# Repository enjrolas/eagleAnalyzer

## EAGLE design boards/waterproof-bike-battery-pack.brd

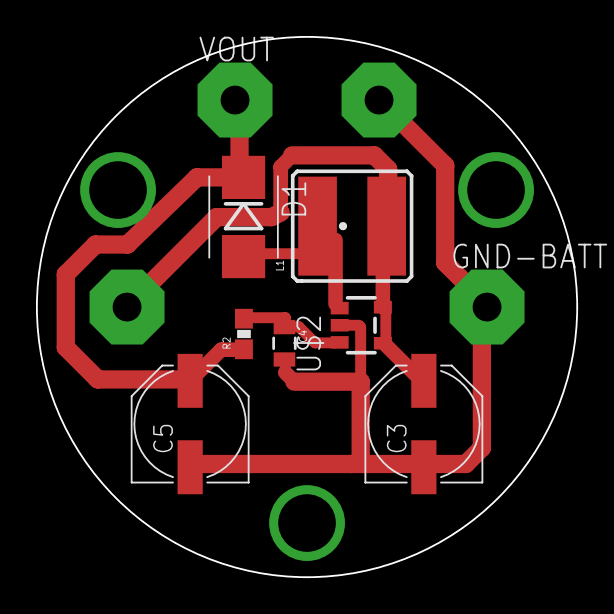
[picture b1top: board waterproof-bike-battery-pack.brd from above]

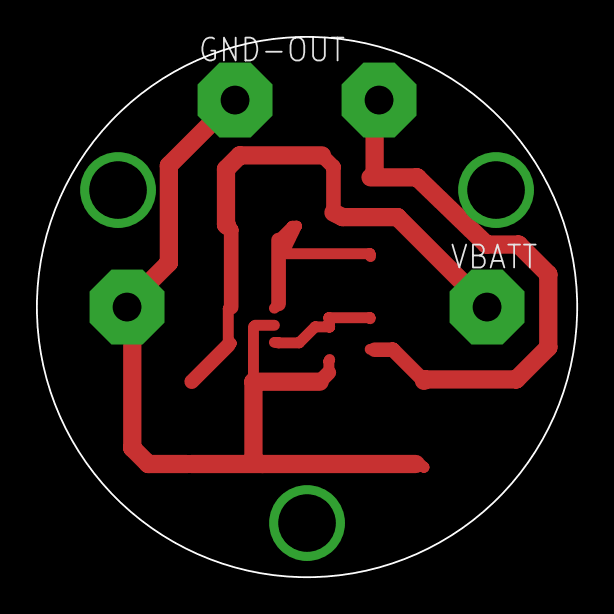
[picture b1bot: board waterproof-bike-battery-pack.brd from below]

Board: 2 copper layers, 30.0 x 30.0 mm, 11 parts (2 on the bottom side), 5 nets.

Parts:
C3, C5: 100uF; PANASONIC_D
C4: 1uF; 0805
D1: ZHCS2000; SMB-DIODE
GND-BATT: 4,16O1,6
GND-OUT: 4,16O1,6
L1: 10uH; CR54
R2: 10; 0603-RES
U$2: SP6641B-L-5-0; SOT23-5
VBATT: 4,16O1,6
VOUT: 4,16O1,6

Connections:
GND: C3.-, C4.2, C5.-, GND-BATT.1, GND-OUT.1, U$2.2
LX: D1.A, L1.P$1, U$2.1
VBATT: C3.+, L1.P$2, U$2.4, U$2.5, VBATT.1
VBOOST: C5.+, D1.C, R2.1, VOUT.1
VOUT: C4.1, R2.2, U$2.3

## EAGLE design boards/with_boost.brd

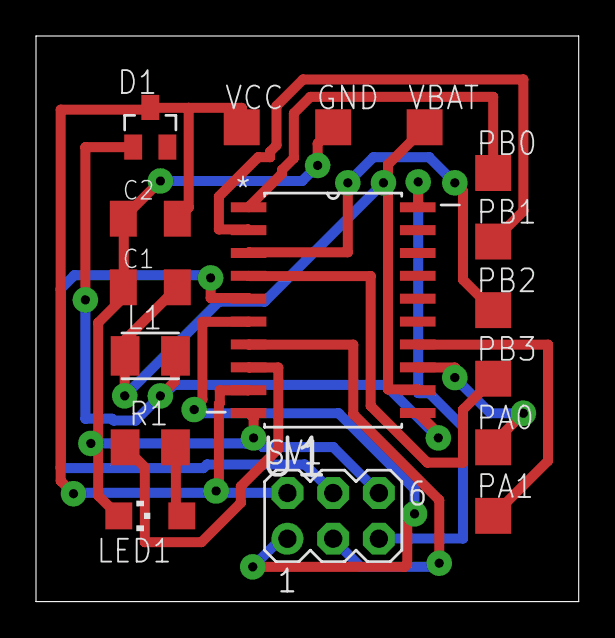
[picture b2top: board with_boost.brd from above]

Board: 2 copper layers, 30.1 x 31.4 mm, 17 parts (0 on the bottom side), 16 nets.

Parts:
C1: 4.7uf; C1206K
C2: 10uf ceramic; C1206K
D1: BAS40; SOT23
GND: TPSQTP20SQ; TP20SQ
L1: 10uh; L3225M
LED1: CHIPLED_1206
PA0, PA1: TPSQTP20SQ; TP20SQ
PB0, PB1, PB2, PB3: TPSQTP20SQ; TP20SQ
R1: 330; M1206
SV1: MA03-2
U1: ATTINY43U; SOIC127P1032X265-20N
VBAT: TPSQTP20SQ; TP20SQ
VCC: TPSQTP20SQ; TP20SQ

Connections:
GND: C1.1, C2.1, GND.TP, LED1.C, SV1.6, U1.10
unnamed: LED1.A, R1.2
unnamed: D1.1, L1.2, U1.11
unnamed: R1.1, U1.8
PA0: PA0.TP, U1.13
PA1: PA1.TP, U1.14
PA7: SV1.5, U1.20
PB0: PB0.TP, U1.1
PB1: PB1.TP, U1.2
PB2: PB2.TP, U1.3
PB3: PB3.TP, U1.4
PB4: SV1.4, U1.5
PB5: SV1.1, U1.6
PB6: SV1.3, U1.7
VBAT: C1.2, L1.1, U1.12, VBAT.TP
VCC: C2.2, D1.3, SV1.2, U1.9, VCC.TP

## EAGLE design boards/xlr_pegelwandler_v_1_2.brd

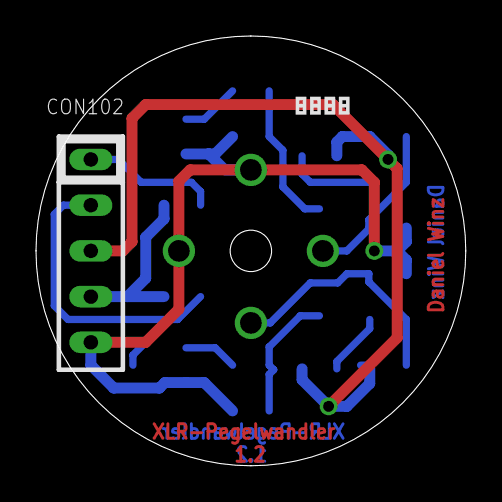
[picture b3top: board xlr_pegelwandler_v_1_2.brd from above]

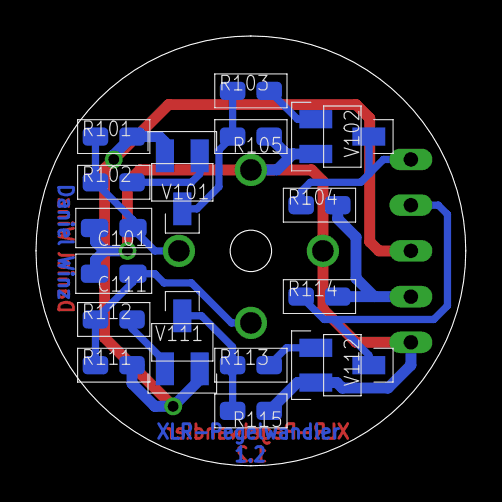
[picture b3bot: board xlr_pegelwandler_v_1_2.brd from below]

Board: 2 copper layers, 23.9 x 23.9 mm, 19 parts (16 on the bottom side), 13 nets.

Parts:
C101, C111: 100n; C_0805
CON101: XLR_NC3MD-V_NEUTRIK
CON102: CON_5X1_100MIL
R101, R111: 330; R_0805
R102, R112: 820k; R_0805
R103, R113: 330k; R_0805
R104, R114: 10k; R_0805
R105, R115: 24k; R_0805
U$1: LP_NUMBER08_SILK_TOP; LP_NUMBER_SILK_TOP
V101, V111: BC857A; SOT23
V102, V112: BC847A; SOT23

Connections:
CON101: C101.P$1, CON101.2, R101.P$1, R102.P$1
unnamed: R103.P$2, V102.1
unnamed: R113.P$2, V112.1
unnamed: CON102.P$2, R114.P$1, V112.3
unnamed: CON102.P$1, R104.P$1, V102.3
unnamed: R102.P$2, V101.1
unnamed: R103.P$1, R105.P$2, V101.3
unnamed: R113.P$1, R115.P$2, V111.3
unnamed: CON102.P$3, R101.P$2, R111.P$2, V101.2, V111.2
unnamed: R112.P$2, V111.1
unnamed: C111.P$1, CON101.3, R111.P$1, R112.P$1
unnamed: CON102.P$4, R104.P$2, R114.P$2
V102: C101.P$2, C111.P$2, CON101.1, CON101.G, CON102.P$5, R105.P$1, R115.P$1, V102.2, V112.2

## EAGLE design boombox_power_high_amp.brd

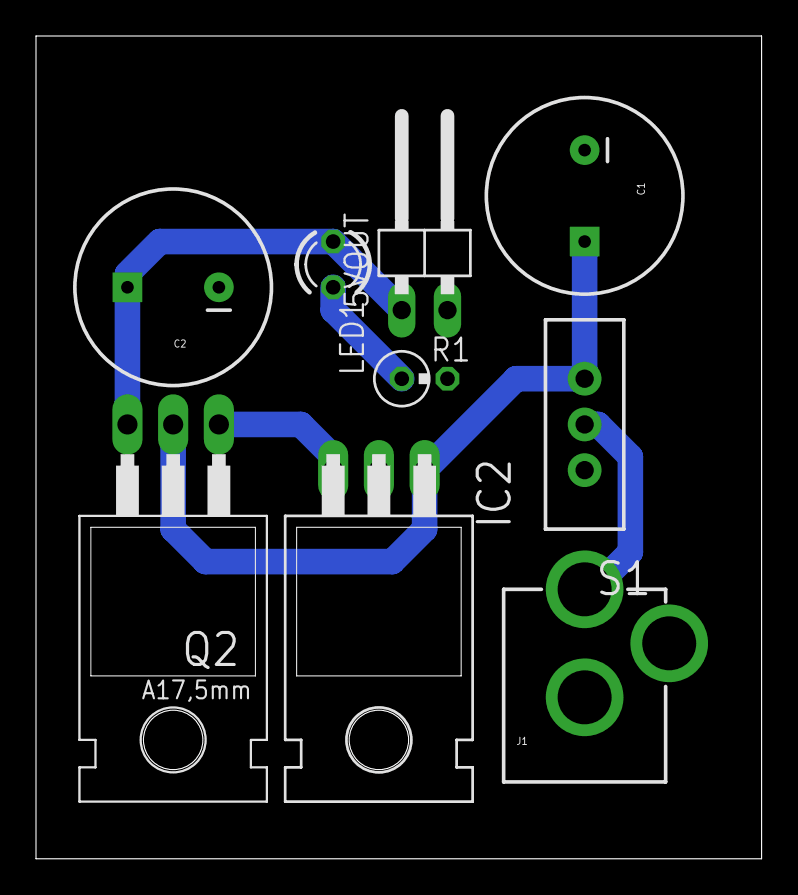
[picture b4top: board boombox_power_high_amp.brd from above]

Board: 2 copper layers, 40.3 x 45.7 mm, 9 parts (0 on the bottom side), 6 nets.

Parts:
5VOUT: 1X02/90
C1, C2: 2200uF; CPOL-RADIAL-1000UF-25V
IC2: 7805T; TO220H
J1: POWER_JACKPTH; POWER_JACK_PTH
LED1: LED3MM
Q2: BD243; TO220
R1: 330R; 0309V
S1: SWITCH-SPDT

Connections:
9V: C1.1, IC2.1, Q2.2, S1.3
GND: 5VOUT.2, C1.2, C2.2, IC2.2, J1.GND, R1.2
unnamed: 5VOUT.1, C2.1, LED1.A, Q2.3
unnamed: LED1.K, R1.1
unnamed: J1.PWR, S1.2
VCC: IC2.3, Q2.1

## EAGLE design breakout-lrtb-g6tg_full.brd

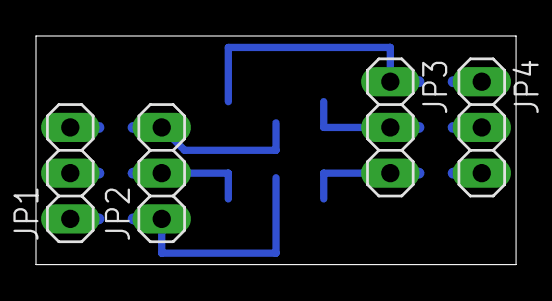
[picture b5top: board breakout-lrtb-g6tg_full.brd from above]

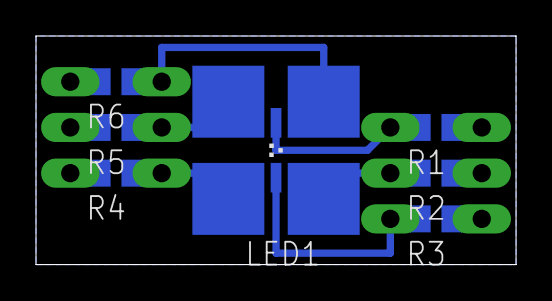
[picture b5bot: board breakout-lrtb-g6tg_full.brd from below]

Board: 2 copper layers, 26.7 x 12.7 mm, 11 parts (7 on the bottom side), 12 nets.

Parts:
JP1, JP2, JP3, JP4: 1X03
LED1: LRTB_G6SG
R1, R2, R3, R4, R5, R6: R0805

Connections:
unnamed: JP4.3, R4.2
unnamed: JP4.2, R5.2
unnamed: JP4.1, R6.2
unnamed: JP3.2, LED1.3, R5.1
unnamed: JP3.3, LED1.4, R4.1
unnamed: JP3.1, LED1.1, R6.1
unnamed: JP2.2, LED1.6, R2.2
unnamed: JP2.1, LED1.5, R3.2
unnamed: JP2.3, LED1.2, R1.2
unnamed: JP1.2, R2.1
unnamed: JP1.1, R3.1
unnamed: JP1.3, R1.1

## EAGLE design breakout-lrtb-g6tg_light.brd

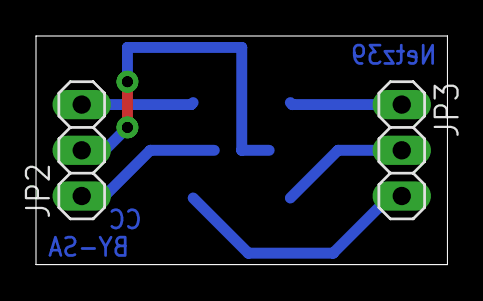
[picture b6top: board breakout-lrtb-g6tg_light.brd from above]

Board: 2 copper layers, 22.9 x 12.7 mm, 3 parts (1 on the bottom side), 6 nets.

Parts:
JP2, JP3: 1X03
LED1: LRTB_G6SG

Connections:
unnamed: JP3.2, LED1.3
unnamed: JP3.3, LED1.4
unnamed: JP3.1, LED1.1
unnamed: JP2.3, LED1.6
unnamed: JP2.1, LED1.5
unnamed: JP2.2, LED1.2

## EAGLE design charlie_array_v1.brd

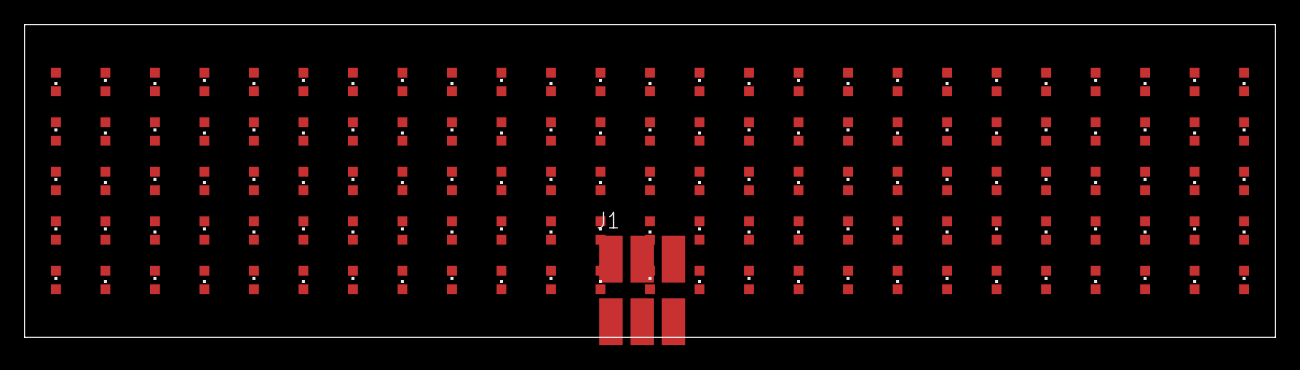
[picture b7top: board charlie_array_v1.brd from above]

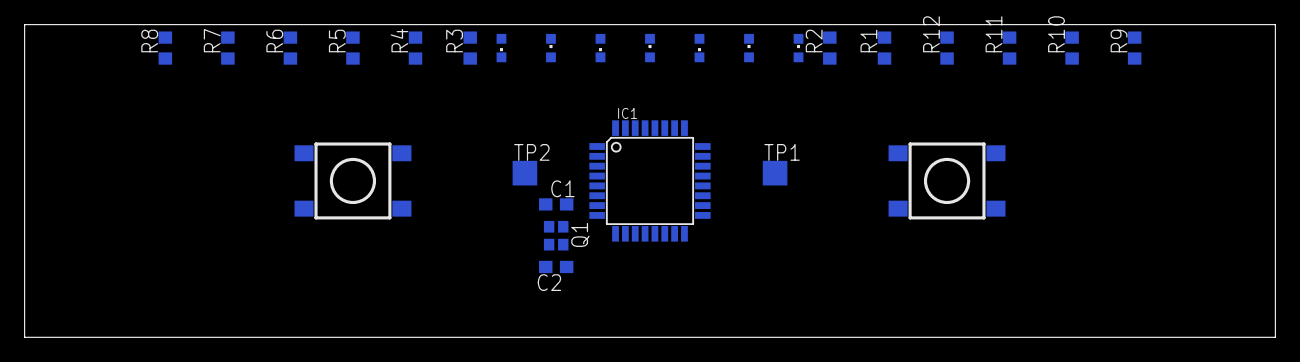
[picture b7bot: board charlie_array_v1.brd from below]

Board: 4 copper layers, 101.6 x 25.4 mm, 153 parts (27 on the bottom side), 34 nets, no tracks yet.

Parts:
C1, C2: C0603
DOWNSW: SWITCH-MOMENTARY-2; TACTILE_SWITCH_TALL
IC1: MEGA8-AI; TQFP32-08
J1: AVR_SPI_PRG_6; 2X3_ICSP_SMD
L1_2, L1_3, L1_4, L1_5, L1_6, L1_7, L1_8, L1_9, L1_10, L1_11, L1_12, L2_1, L2_3, L2_4, L2_5, L2_6, L2_7, L2_8, L2_9, L2_10, L2_11, L2_12, L3_1, L3_2, L3_4, L3_5, L3_6, L3_7, L3_8, L3_9, L3_10, L3_11, L3_12, L4_1, L4_2, L4_3, L4_5, L4_6, L4_7, L4_8, L4_9, L4_10, L4_11, L4_12, L5_1, L5_2, L5_3, L5_4, L5_6, L5_7, L5_8, L5_9, L5_10, L5_11, L5_12, L6_1, L6_2, L6_3, L6_4, L6_5, L6_7, L6_8, L6_9, L6_10, L6_11, L6_12, L7_1, L7_2, L7_3, L7_4, L7_5, L7_6, L7_8, L7_9, L7_10, L7_11, L7_12, L8_1, L8_2, L8_3, L8_4, L8_5, L8_6, L8_7, L8_9, L8_10, L8_11, L8_12, L9_1, L9_2, L9_3, L9_4, L9_5, L9_6, L9_7, L9_8, L9_10, L9_11, L9_12, L10_1, L10_2, L10_3, L10_4, L10_5, L10_6, L10_7, L10_8, L10_9, L10_11, L10_12, L11_1, L11_2, L11_3, L11_4, L11_5, L11_6, L11_7, L11_8, L11_9, L11_10, L11_12, L12_1, L12_2, L12_3, L12_4, L12_5, L12_6, L12_7, L12_8, L12_9, L12_10, L12_11: CHIPLED_0603
Q1: FA-128
R1, R2, R3, R4, R5, R6, R7, R8, R9, R10, R11, R12: R0603
TP1, TP2: TPTP20SQ; TP20SQ
UPSW: SWITCH-MOMENTARY-2; TACTILE_SWITCH_TALL

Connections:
+5V: IC1.4, IC1.6, J1.P$2, TP2.TP
D1: IC1.30, R1.1
D2: IC1.31, R2.1
D3: IC1.32, R3.1
D4: IC1.1, R4.1
D5: IC1.2, R5.1
D6: IC1.9, R6.1
D7: IC1.10, R7.1
D8: IC1.11, R8.1
D9: IC1.23, R9.1
D10: IC1.24, R10.1
D11: IC1.25, R11.1
D12: IC1.26, R12.1
DR1: L1_2.A, L1_3.A, L1_4.A, L1_5.A, L1_6.A, L1_7.A, L1_8.A, L1_9.A, L1_10.A, L1_11.A, L1_12.A, L2_1.C, L3_1.C, L4_1.C, L5_1.C, L6_1.C, L7_1.C, L8_1.C, L9_1.C, L10_1.C, L11_1.C, L12_1.C, R1.2
DR2: L1_2.C, L2_1.A, L2_3.A, L2_4.A, L2_5.A, L2_6.A, L2_7.A, L2_8.A, L2_9.A, L2_10.A, L2_11.A, L2_12.A, L3_2.C, L4_2.C, L5_2.C, L6_2.C, L7_2.C, L8_2.C, L9_2.C, L10_2.C, L11_2.C, L12_2.C, R2.2
DR3: L1_3.C, L2_3.C, L3_1.A, L3_2.A, L3_4.A, L3_5.A, L3_6.A, L3_7.A, L3_8.A, L3_9.A, L3_10.A, L3_11.A, L3_12.A, L4_3.C, L5_3.C, L6_3.C, L7_3.C, L8_3.C, L9_3.C, L10_3.C, L11_3.C, L12_3.C, R3.2
DR4: L1_4.C, L2_4.C, L3_4.C, L4_1.A, L4_2.A, L4_3.A, L4_5.A, L4_6.A, L4_7.A, L4_8.A, L4_9.A, L4_10.A, L4_11.A, L4_12.A, L5_4.C, L6_4.C, L7_4.C, L8_4.C, L9_4.C, L10_4.C, L11_4.C, L12_4.C, R4.2
DR5: L1_5.C, L2_5.C, L3_5.C, L4_5.C, L5_1.A, L5_2.A, L5_3.A, L5_4.A, L5_6.A, L5_7.A, L5_8.A, L5_9.A, L5_10.A, L5_11.A, L5_12.A, L6_5.C, L7_5.C, L8_5.C, L9_5.C, L10_5.C, L11_5.C, L12_5.C, R5.2
DR6: L1_6.C, L2_6.C, L3_6.C, L4_6.C, L5_6.C, L6_1.A, L6_2.A, L6_3.A, L6_4.A, L6_5.A, L6_7.A, L6_8.A, L6_9.A, L6_10.A, L6_11.A, L6_12.A, L7_6.C, L8_6.C, L9_6.C, L10_6.C, L11_6.C, L12_6.C, R6.2
DR7: L1_7.C, L2_7.C, L3_7.C, L4_7.C, L5_7.C, L6_7.C, L7_1.A, L7_2.A, L7_3.A, L7_4.A, L7_5.A, L7_6.A, L7_8.A, L7_9.A, L7_10.A, L7_11.A, L7_12.A, L8_7.C, L9_7.C, L10_7.C, L11_7.C, L12_7.C, R7.2
DR8: L1_8.C, L2_8.C, L3_8.C, L4_8.C, L5_8.C, L6_8.C, L7_8.C, L8_1.A, L8_2.A, L8_3.A, L8_4.A, L8_5.A, L8_6.A, L8_7.A, L8_9.A, L8_10.A, L8_11.A, L8_12.A, L9_8.C, L10_8.C, L11_8.C, L12_8.C, R8.2
DR9: L1_9.C, L2_9.C, L3_9.C, L4_9.C, L5_9.C, L6_9.C, L7_9.C, L8_9.C, L9_1.A, L9_2.A, L9_3.A, L9_4.A, L9_5.A, L9_6.A, L9_7.A, L9_8.A, L9_10.A, L9_11.A, L9_12.A, L10_9.C, L11_9.C, L12_9.C, R9.2
DR10: L1_10.C, L2_10.C, L3_10.C, L4_10.C, L5_10.C, L6_10.C, L7_10.C, L8_10.C, L9_10.C, L10_1.A, L10_2.A, L10_3.A, L10_4.A, L10_5.A, L10_6.A, L10_7.A, L10_8.A, L10_9.A, L10_11.A, L10_12.A, L11_10.C, L12_10.C, R10.2
DR11: L1_11.C, L2_11.C, L3_11.C, L4_11.C, L5_11.C, L6_11.C, L7_11.C, L8_11.C, L9_11.C, L10_11.C, L11_1.A, L11_2.A, L11_3.A, L11_4.A, L11_5.A, L11_6.A, L11_7.A, L11_8.A, L11_9.A, L11_10.A, L11_12.A, L12_11.C, R11.2
DR12: L1_12.C, L2_12.C, L3_12.C, L4_12.C, L5_12.C, L6_12.C, L7_12.C, L8_12.C, L9_12.C, L10_12.C, L11_12.C, L12_1.A, L12_2.A, L12_3.A, L12_4.A, L12_5.A, L12_6.A, L12_7.A, L12_8.A, L12_9.A, L12_10.A, L12_11.A, R12.2
GNDA: C1.2, C2.2, DOWNSW.B2, IC1.3, IC1.5, IC1.21, J1.P$7, TP1.TP, UPSW.B2
MISO: IC1.16, J1.P$1
MOSI: IC1.15, J1.P$4
unnamed: C2.1, IC1.8, Q1.3
unnamed: IC1.14, UPSW.A2
unnamed: DOWNSW.A2, IC1.13
unnamed: C1.1, IC1.7, Q1.1
RESET: IC1.29, J1.P$5
SCK: IC1.17, J1.P$3

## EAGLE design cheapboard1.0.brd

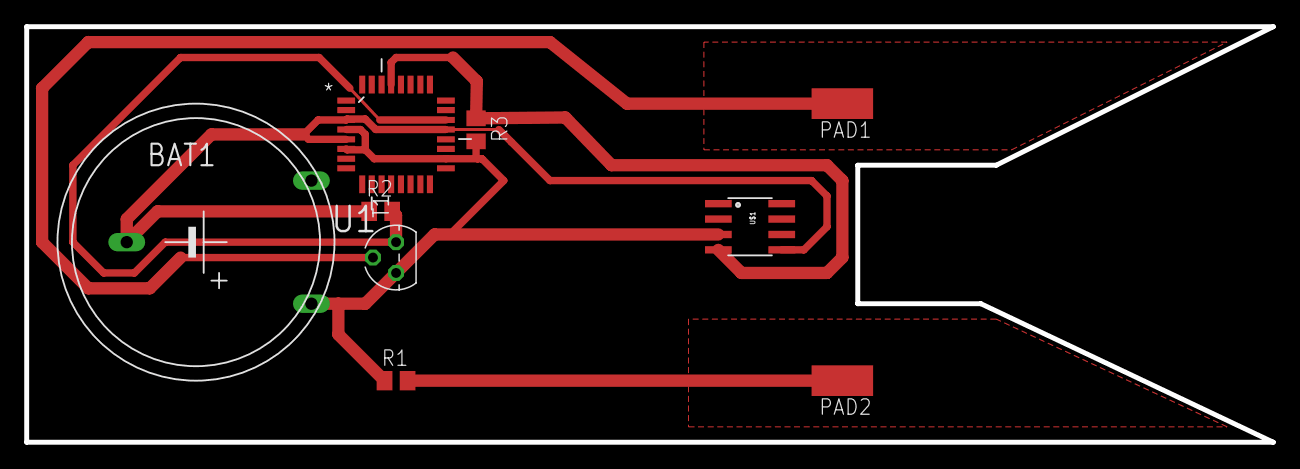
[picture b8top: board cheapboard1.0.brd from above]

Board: 2 copper layers, 102.9 x 34.3 mm, 9 parts (0 on the bottom side), 6 nets.

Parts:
BAT1: BATTERY
PAD1, PAD2: SMD2,54-5,08
R1, R2, R3: M0805
T1: BC547; TO92
U1: ATMEGA48A-AU; QFP80P900X900X120-32N
U$1: DS1820SOIC; DS18B20_SOIC

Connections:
GND: BAT1.-, R2.1, U1.3, U1.5, U1.21, U$1.GND
unnamed: BAT1.+, R1.1, R3.2, T1.3, U1.4, U1.6, U1.18, U$1.VCC
unnamed: R2.2, T1.1, U1.22
unnamed: R3.1, U1.29, U$1.DQ
PAD1: PAD1.1, T1.2
PAD2: PAD2.1, R1.2

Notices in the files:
parts and their libraries:
SparkFun: Licensing: CC v3.0 Share-Alike You are welcome to use this library for commercial purposes.
